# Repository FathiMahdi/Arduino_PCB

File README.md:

# Arduino_PCB
- Published by: FATHI MAHDI ELSIDDIG HAROUN (Aptex96).
- Published in 21/June/2021.
- Open source design for arduino board
- Feel Free to adding modifing the project.
- For serious work please refere to this repository.
- Circuit intgrity not guranteed.
- Not tesed circuit.
- PCB routing not provided.

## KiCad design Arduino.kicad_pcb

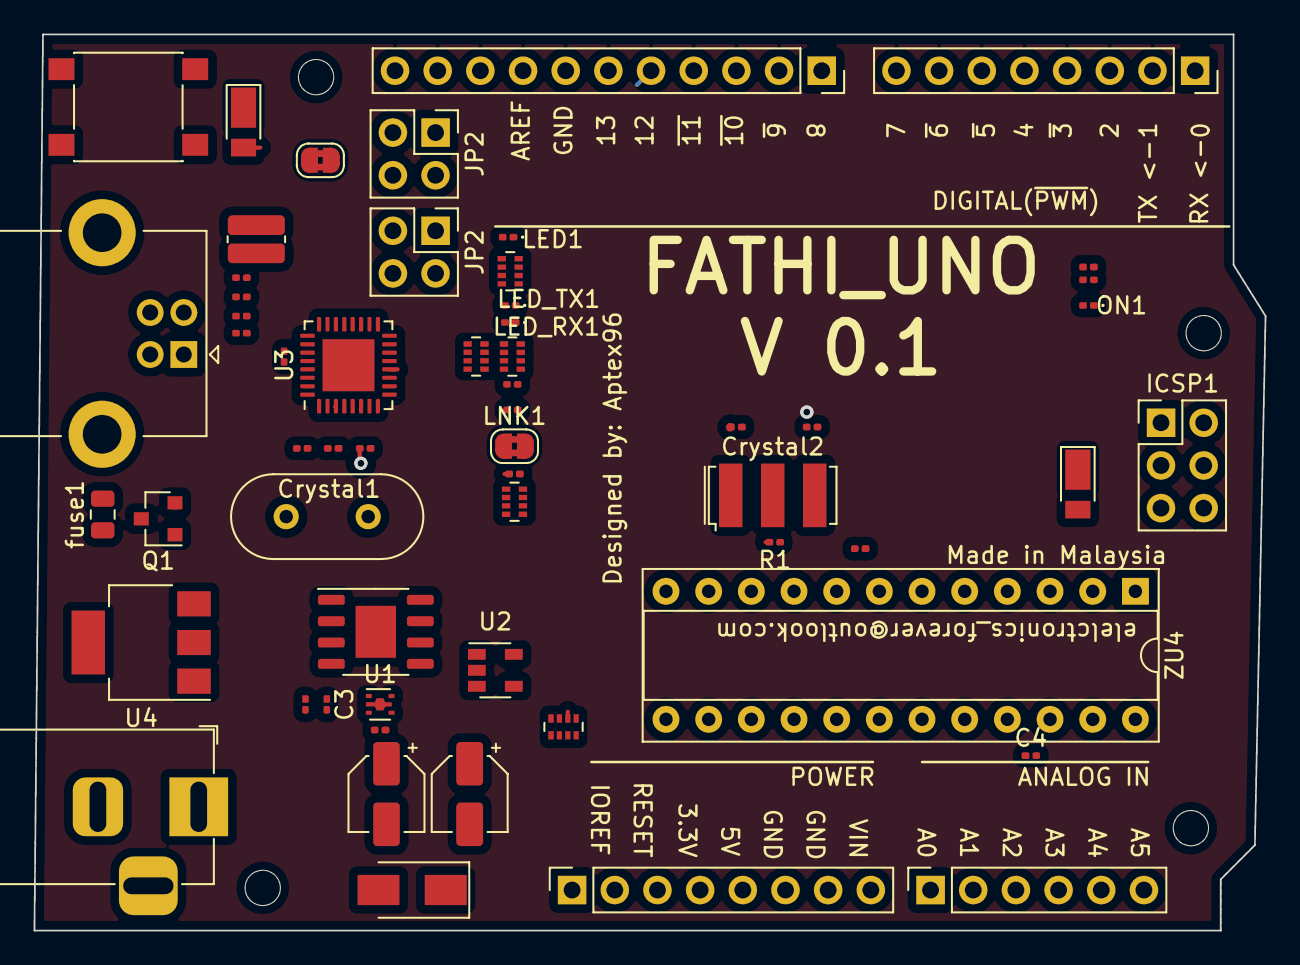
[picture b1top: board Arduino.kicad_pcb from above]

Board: 4 copper layers, 73.3 x 53.3 mm, 62 parts (0 on the bottom side), 58 nets.

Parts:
AD1: 6x1F -H8.5; PinSocket_1x06_P2.54mm_Vertical
C1, C2, C9, C11: 22P; C_0201_0603Metric
C3, C8: 1u; C_0201_0603Metric
C4, C5, C6: 100n; C_0201_0603Metric
Crystal1: 16MHz; Crystal_HC49-4H_Vertical
Crystal2: 16MHz; Resonator_SMD-3Pin_7.2x3.0mm
D1: M7; D_SMA
D2: CD1206; D_PowerDI-123
D3: D_Small; D_PowerDI-123
FB1: Ferrite_Bead_Small; R_0612_1632Metric_Pad1.18x3.40mm_HandSolder
H0, H2, H3: hole; MountingHole_2.1mm
ICSP1: 3x2 M; PinHeader_2x03_P2.54mm_Vertical
IOH1: 10x1F -H8.5; PinSocket_1x11_P2.54mm_Vertical
IOL1: 8x1F -H8.5; PinSocket_1x08_P2.54mm_Vertical
JP2, JP2#2: 2x2 M - NM; PinHeader_2x02_P2.54mm_Vertical
LED1: YELLOW; LED_0201_0603Metric
LED_RX1: YELLOW; LED_0201_0603Metric
LED_TX1: YELLOW; LED_0201_0603Metric
LNK1: LINK1; SolderJumper-2_P1.3mm_Bridged2Bar_RoundedPad1.0x1.5mm
LNK2: LINKW; SolderJumper-2_P1.3mm_Bridged2Bar_RoundedPad1.0x1.5mm
ON1: GREEN; LED_0201_0603Metric
PC1: 47U; CP_Elec_4x3
PC2: 47u; CP_Elec_4x3
POWE_HEADER1: 8x1F -H8.5; PinSocket_1x08_P2.54mm_Vertical
Q1: FDN340P; SOT-23
R1, R2: 1M; R_0201_0603Metric
R1NB1: 10K; R_0201_0603Metric
RN1A1: 10K; R_0201_0603Metric
RN1D1: 10k; R_0201_0603Metric
RN2A1, RN2A2, RN2B1, RN2C1: 1K; R_Array_Concave_4x0402
RN2D1: 1k; R_Array_Concave_4x0402
RN3A1, RN3D1: 22R; R_0201_0603Metric
RN4B1, RN4C1: 1K; R_0201_0603Metric
RN4D1: 1k; R_0201_0603Metric
RV1: Varistor; R_0201_0603Metric
SW1: SW_Push_Dual; SW_SPST_PTS645
U1: LMV358; HVSOF5
U2: LP2985-3.3; SOT-23-5
U3: ATmega16U2-MU; QFN-32-1EP_5x5mm_P0.5mm_EP3.1x3.1mm
U4: NCP1117-5.0_SOT223; SOT-223-3_TabPin2
U5B1: LMV358; HSOP-8-1EP_3.9x4.9mm_P1.27mm_EP2.41x3.1mm
USB_B1: USB_B; USB_B_Lumberg_2411_02_Horizontal
X1: POWERSUPPLY_DC21MMX; BarrelJack_Horizontal
Z1: CG060EMLC; R_0201_0603Metric
ZU4: ATmega328P-PU; DIP-24_W7.62mm_Socket
fuse1: 500mA; Fuse_0805_2012Metric
h1: hole; MountingHole_2.1mm

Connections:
+3V3: C3.1, POWE_HEADER1.4, U1.2, U2.5
+5V: C6.1, D2.1, D3.1, ICSP1.2, PC2.1, POWE_HEADER1.2, POWE_HEADER1.5, Q1.2, RN1D1.1, RN2B1.2, RN2C1.2, RN4C1.1, RN4D1.1, U2.1, U2.3, U3.4, U3.32, U4.2, ZU4.7, ZU4.20
/AD0: AD1.1, ZU4.23
/AD1: AD1.2, ZU4.24
/LED_RX: LED_RX1.1, U3.10
/LED_TX: LED_TX1.1, U3.11
/M8RXD: RN4B1.2, U3.9
/M8TXD: RN2A2.2, U3.8
/PB0: ICSP1.3, U3.14, U3.15
/PB3: JP2.3, JP2#2.3, U3.19
/PB4: JP2.1, JP2#2.1, U3.18
/PB6: JP2.2, JP2#2.2, U3.20
/PB7: JP2.4, JP2#2.4, U3.21
/PD0: IOL1.1, RN4B1.1, U3.6, ZU4.2
/PD1: IOL1.2, RN2A2.1, U3.7, ZU4.3
/PD2: IOL1.3, ZU4.4
/PD3: IOL1.4, ZU4.5
/PD4: IOL1.5, ZU4.6
/PD5: IOL1.6, ZU4.11
/PD6: IOL1.7, U3.12, ZU4.12
/PWRIN: D1.2, X1.1
/UCAP: C8.1, U3.27
AREF: C4.1, IOH1.8, ZU4.21
D+: RN3D1.2, U3.29
D-: RN3A1.2, U3.30
GND: C1.2, C2.2, C3.2, C4.2, C6.2, C9.2, C11.2, FB1.1, ICSP1.6, IOH1.7, LED1.1, LNK2.2, ON1.1, PC1.2, PC2.2, POWE_HEADER1.6, POWE_HEADER1.7, R1NB1.1, RN2D1.1, RV1.2, U2.2, U3.3, U3.33, U4.1, USB_B1.4, USB_B1.5, X1.2, Z1.2, ZU4.8, ZU4.22
MISO2: ICSP1.1, U3.17
MOSI2: ICSP1.4, U3.16
unnamed: C5.1, LNK1.1
unnamed: D1.1, PC1.1, U4.3
unnamed: IOH1.1, ZU4.14
unnamed: IOH1.2, ZU4.15
unnamed: IOH1.3, ZU4.16
unnamed: IOH1.4, ZU4.17
unnamed: IOH1.5, ZU4.18
unnamed: LED1.2, RN2A1.1
unnamed: LED_RX1.2, RN2C1.1
unnamed: LED_TX1.2, RN2B1.1
unnamed: ON1.2, RN4C1.2, RN4D1.2
unnamed: Q1.1, U1.1
unnamed: R1NB1.2, RN1A1.1, U1.3
unnamed: RN2A1.2, U5B1.1, U5B1.2
unnamed: RN3A1.1, RV1.1, USB_B1.2
unnamed: RN3D1.1, USB_B1.3, Z1.1
unnamed: USB_B1.1, fuse1.1
PD7: C5.2, IOL1.8, RN2D1.2, U3.13, ZU4.13
RESET1: D2.2, LNK1.2, RN1D1.2, U3.23, ZU4.1
RESET2: D3.2, ICSP1.5, POWE_HEADER1.3, SW1.2, U3.24
SCK: IOH1.6, U5B1.3, ZU4.19
SCL: AD1.6, IOH1.10
SDA: AD1.5, IOH1.9
UGND: C8.2, FB1.2, LNK2.1, U3.28
UVCC: Q1.3, U3.31, fuse1.2
VIN: POWE_HEADER1.8, RN1A1.2
XTAL1: C11.1, Crystal2.2, R1.1, ZU4.9
XTAL1_USB: C1.1, Crystal1.2, R2.1, U3.1
XTAL2: C9.1, Crystal2.1, R1.2, ZU4.10
XTAL2_USB: C2.1, Crystal1.1, R2.2, U3.2

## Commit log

2021-06-20 Adding V0.1
2021-06-20 Adding scematic image
    Adding scematic image
